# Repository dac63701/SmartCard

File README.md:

# Smart Card
A nRF54L15 based Bluetooth Tracker in a Credit Card sized package

The goal of this project was to create a small and slim Bluetooth tracker that would fit into a credit card enclosure. To do this, a 0.8mm thin 80mah battery was used along with a 0.8mm PCB. The device makes use of wireless charging with a BQ51013B so that it is easy to use and keep charged. There is also a custom battery charger and protection circuit. It uses a BQ298009 for protection and a BQ25100 for charging. Finally there is a TPS62840 for sourcing 1v8 from the battery and the antenna along with a matching network.

## Components
Check the [bom](https://github.com/dac63701/SmartCard/blob/main/production/bom.csv) for more details on the PCB components.
Standard PLA was used for the Prototype case.
The battery is a 084545 battery from [Alibaba](https://www.alibaba.com/product-detail/GEB-ultra-0-8mm-Thickness-084545_1601492203632.html?spm=a2756.trade-list-buyer.0.0.5fea76e93Ynkdn).

## Case Files
Check [OnShape](https://cad.onshape.com/documents/73dd8871ae024b497bb44b73/w/69cf76015be0ecbff129bf07/e/5547e5b9bb5f69b8ddd4b47d?renderMode=0&uiState=6a8e2710a56b25790309a2e5) for the files.

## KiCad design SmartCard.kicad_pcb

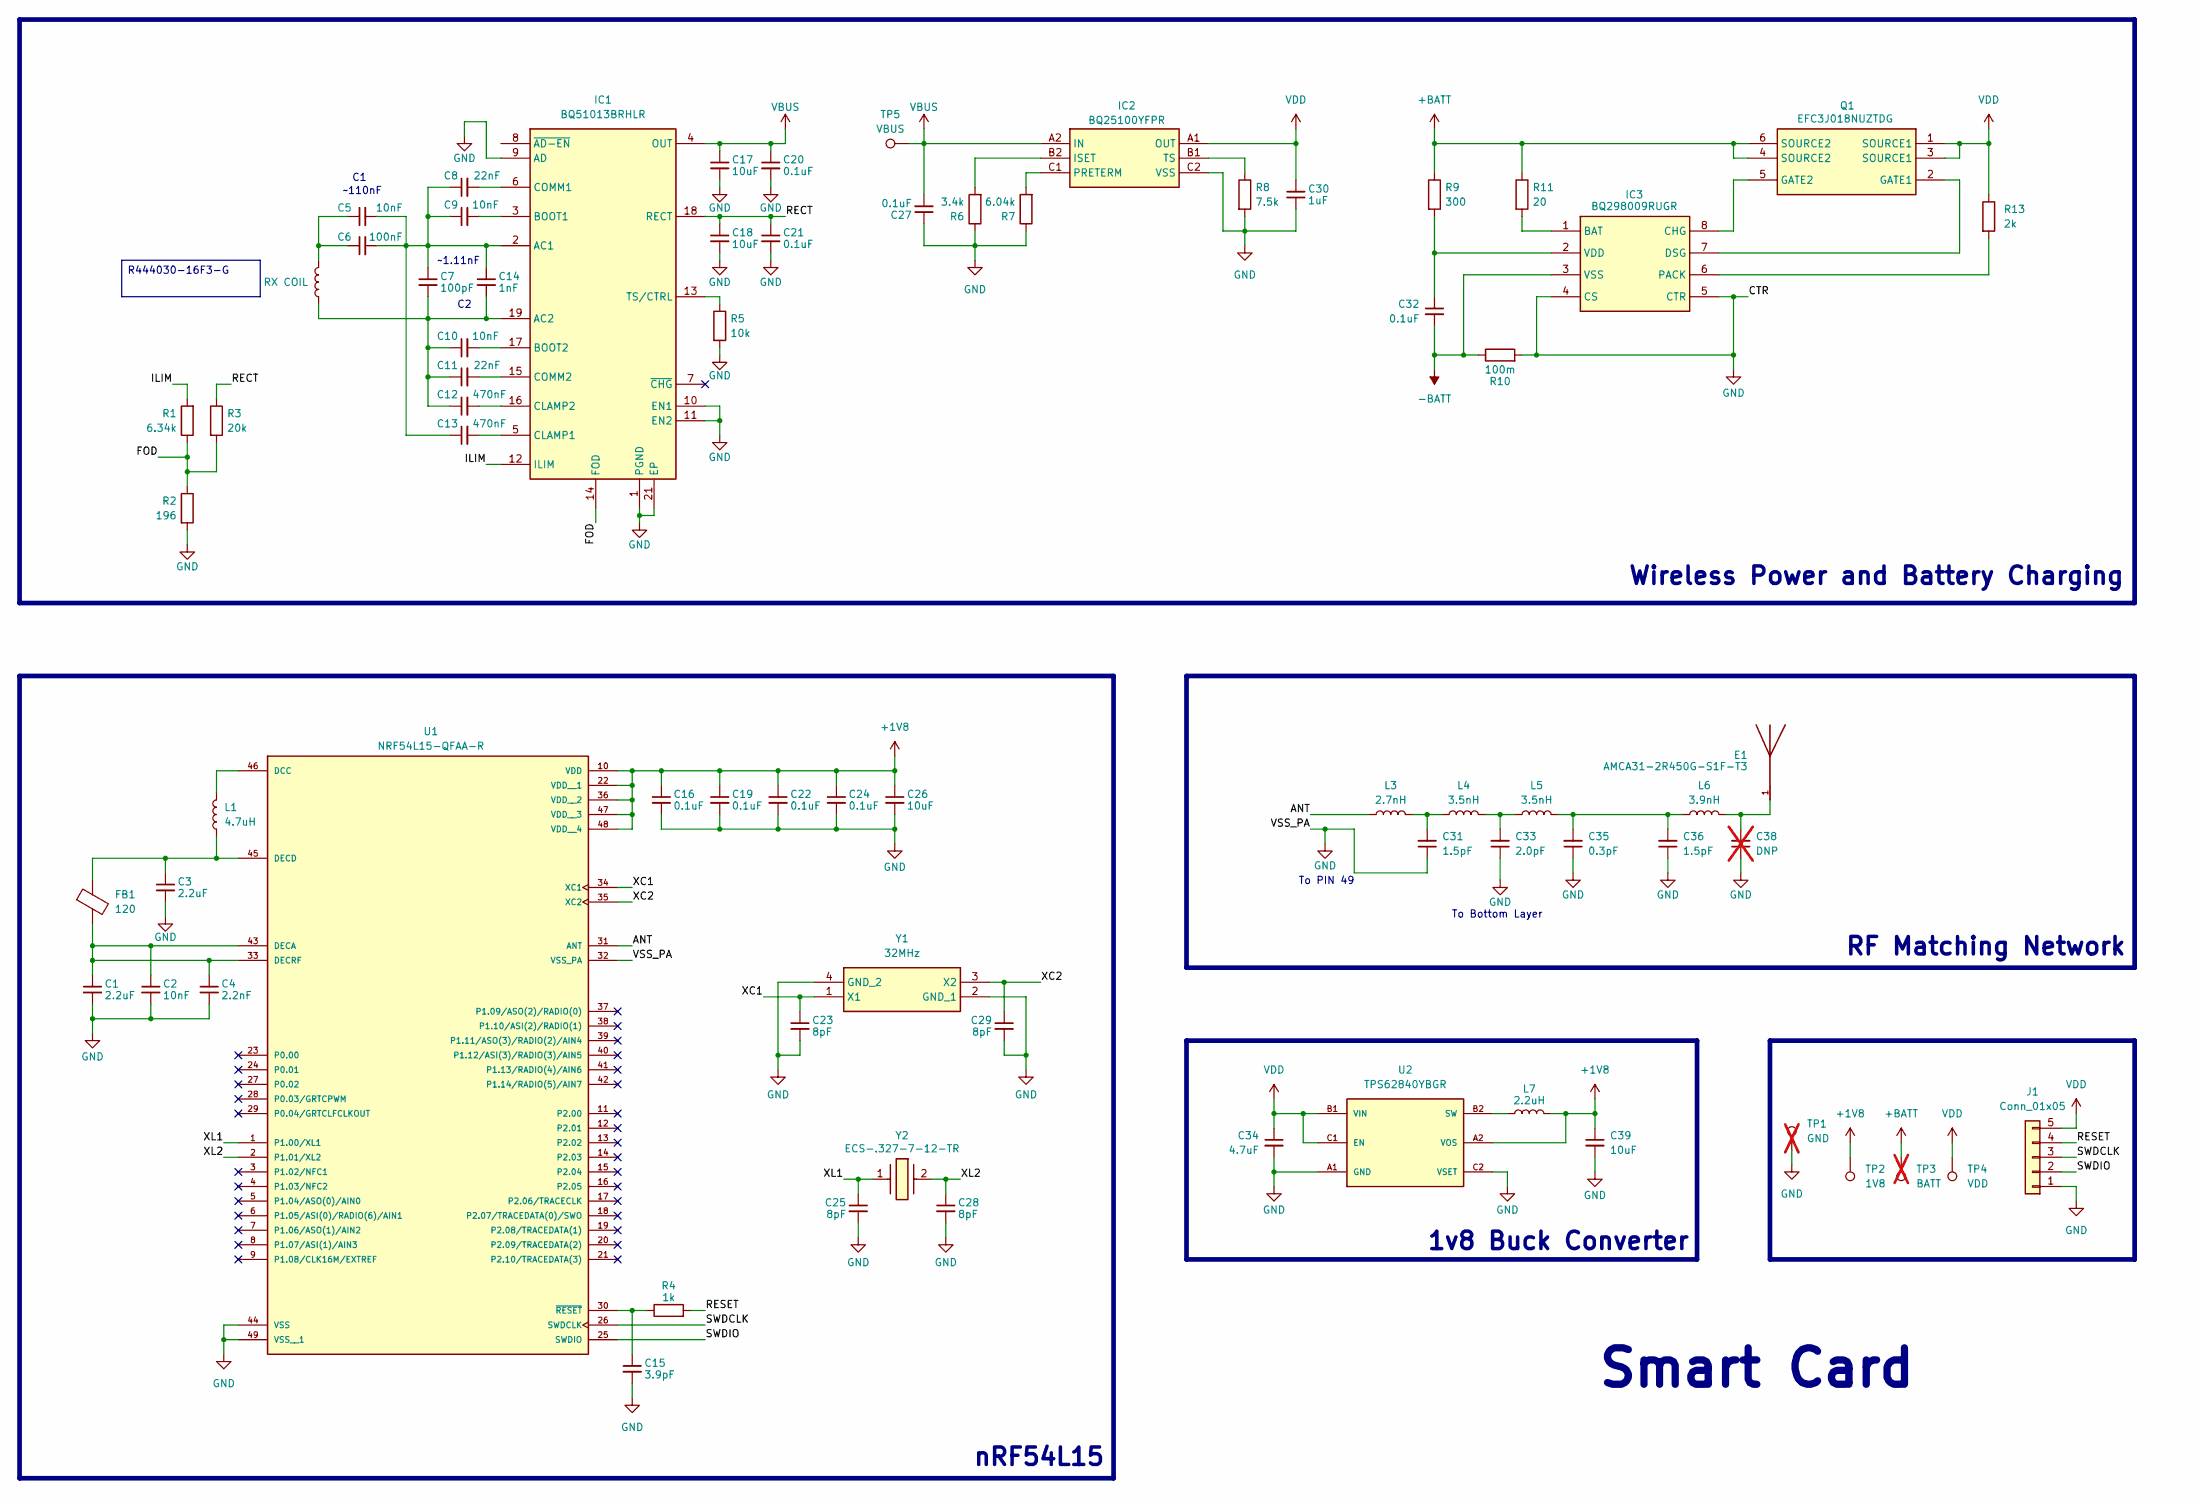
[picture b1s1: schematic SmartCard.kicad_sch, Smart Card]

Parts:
C1, C3: 2.2uF; C_0402_1005Metric; MPN GRM155D80J225ME95D
C2, C9, C10: 10nF; C_0402_1005Metric; MPN GRM155R71H103KA88D
C4: 2.2nF; C_0402_1005Metric; MPN GRM155R71C223KA01D
C5: 10nF; C_0603_1608Metric; MPN GRM155R71H103KA88D
C6: 100nF; C_0603_1608Metric; MPN GRM155R71H104KE14D
C7: 100pF; C_0603_1608Metric; MPN GRM155R71H331KA01D
C8, C11: 22nF; C_0402_1005Metric; MPN GRM155R71H223KA12D
C12, C13: 470nF; C_0402_1005Metric; MPN C1005X5R1E474K050BB
C14: 1nF; C_0603_1608Metric; MPN GRM155R71H102KA01D
C15: 3.9pF; C_0402_1005Metric; MPN GRM1555C1H3R9BA01D
C16, C19, C20, C21, C22, C24, C27, C32: 0.1uF; C_0402_1005Metric; MPN GRM155R71H104KE14D
C17, C18, C26, C39: 10uF; C_0603_1608Metric; MPN GRT188R61E106ME13D
C23, C25, C28, C29: 8pF; C_0402_1005Metric; MPN GJM1555C1H8R0BB01D
C30: 1uF; C_0603_1608Metric; MPN EMK105BJ105KV-F
C31, C36: 1.5pF; C_0201_0603Metric; MPN GJM0335C1E1R5WB01D
C33: 2.0pF; C_0201_0603Metric; MPN GRM0335C1H2R0WA01D
C34: 4.7uF; C_0603_1608Metric; MPN GMC10X5R475K10NT
C35: 0.3pF; C_0201_0603Metric; MPN GRM0335C1ER30WA01D
C38: DNP; C_0201_0603Metric; MPN DNP; not fitted
E1: AMCA31-2R450G-S1F-T3; XDCR_AMCA31-2R450G-S1F-T3; PARTREV 03-21-19
FB1: 120; L_0402_1005Metric; MPN 2504021217Y0
IC1: BQ51013BRHLR; Texas_VQFN-RHL-20; Mouser Part Number 595-BQ51013BRHLR
IC2: BQ25100YFPR; BGA6C40P2X3_88X158X50; Mouser Part Number 595-BQ25100YFPR
IC3: BQ298009RUGR; Mouser Part Number 595-BQ298009RUGR
J1: Conn_01x05; PinHeader_1x05_P2.54mm_Vertical
L1: 4.7uH; L_0603_1608Metric; MPN MLZ1608CWC4R7MTD25
L2: RX COIL; L_1812_4532Metric_Pad1.30x3.40mm_HandSolder; MPN WR444030-16F3-G
L3: 2.7nH; L_0201_0603Metric; MPN LQP03HQ2N7B02D
L4, L5: 3.5nH; L_0201_0603Metric; MPN LQP03HQ3N5B02D
L6: 3.9nH; L_0201_0603Metric; MPN LQP03TQ3N9B02D
L7: 2.2uH; L_0603_1608Metric; MPN LQM18PN2R2MGHD
Q1: EFC3J018NUZTDG; Mouser Part Number 863-EFC3J018NUZTDG
R1: 6.34k; R_0402_1005Metric; MPN RC0402FR-076K34L
R2: 196; R_0402_1005Metric; MPN CRCW0402196RFKED
R3: 20k; R_0402_1005Metric; MPN RC0402FR-0720KL
R4: 1k; R_0402_1005Metric; MPN RC0402FR-071KL
R5: 10k; R_0402_1005Metric; MPN RC0402FR-0710KL
R6: 3.4k; R_0402_1005Metric; MPN RC0402FR-073K4L
R7: 6.04k; R_0402_1005Metric; MPN RC0402FR-076K04L
R8: 7.5k; R_0402_1005Metric; MPN RC0402FR-077K5L
R9: 300; R_0402_1005Metric; MPN RC0402FR-07300RL
R10: 100m; R_0805_2012Metric; MPN RL1220S-R10-F
R11: 20; R_0402_1005Metric; MPN RC0402FR-0720RL
R13: 2k; R_0402_1005Metric; MPN RC0402FR-0720KL
TP1: GND; TestPoint_Pad_2.0x2.0mm; not fitted
TP2: 1V8; TestPoint_Pad_2.0x2.0mm
TP3: BATT; TestPoint_Pad_2.0x2.0mm; not fitted
TP4: VDD; TestPoint_Pad_2.0x2.0mm
TP5: VBUS; TestPoint_Pad_2.0x2.0mm
U1: NRF54L15-QFAA-R; QFN40P600X600X90-49N; PARTREV 0.8
U2: TPS62840YBGR; PARTREV D
Y1: 32MHz; ABM11W300000MHZ4B1UT3; Manufacturer_Part_Number ABM11W-25.0000MHZ-7-D1X-T3
Y2: ECS-.327-7-12-TR; ECS327712TR; Mouser Part Number 520-ECS-.327-7-12-TR

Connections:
+1V8: C16.1, C19.1, C22.1, C24.1, C26.1, C39.1, L7.2, TP2.1 (1_1), U1.10 (VDD), U1.22 (VDD__1), U1.36 (VDD__2), U1.47 (VDD__3), U1.48 (VDD__4), U2.A2 (VOS)
+BATT: Q1.4 (SOURCE2), Q1.6 (SOURCE2), R9.1, R11.1, TP3.1
-BATT: C32.2, IC3.3 (VSS), R10.1
/ANT: L3.1, U1.31 (ANT)
/FOD: IC1.14 (FOD), R1.1, R2.1, R3.2
/ILIM: IC1.12 (ILIM), R1.2
/RECT: C18.1, C21.1, IC1.18 (RECT), R3.1
/RESET: J1.4, R4.2
/SWDCLK: J1.3, U1.26 (SWDCLK)
/SWDIO: J1.2, U1.25 (SWDIO)
/XC1: C23.1, U1.34 (XC1), Y1.1 (X1)
/XC2: C29.1, U1.35 (XC2), Y1.3 (X2)
/XL1: C25.1, U1.1 (P1.00/XL1), Y2.1
/XL2: C28.1, U1.2 (P1.01/XL2), Y2.2 (OUT/IN_2)
GND: C1.2, C2.2, C3.2, C4.2, C15.2, C16.2, C17.2, C18.2, C19.2, C20.2, C21.2, C22.2, C23.2, C24.2, C25.2, C26.2, C27.1, C28.2, C29.2, C30.2, C31.1, C33.1, C34.2, C35.1, C36.1, C38.1, C39.2, IC1.1 (PGND), IC1.9 (AD), IC1.10 (EN1), IC1.11 (EN2), IC1.20 (PGND), IC1.21 (EP), IC2.C2 (VSS), IC3.4 (CS), IC3.5 (CTR), J1.1, R2.2, R5.2, R6.1, R7.1, R8.2, R10.2, TP1.1, U1.32 (VSS_PA), U1.44 (VSS), U1.49 (VSS__1), U2.A1 (GND), U2.C2 (VSET), Y1.2 (GND_1), Y1.4 (GND_2)
unnamed: C5.1, C6.1, L2.2
unnamed: C31.2, L3.2, L4.1
unnamed: C33.2, L4.2, L5.1
unnamed: C35.2, C36.2, L5.2, L6.1
unnamed: C38.2, E1.1, L6.2
unnamed: C5.2, C6.2, C7.1, C8.1, C9.1, C13.1, C14.1, IC1.2 (AC1)
unnamed: C7.2, C10.1, C11.1, C12.1, C14.2, IC1.19 (AC2), L2.1
unnamed: C9.2, IC1.3 (BOOT1)
unnamed: C10.2, IC1.17 (BOOT2)
unnamed: C13.2, IC1.5 (CLAMP1)
unnamed: C12.2, IC1.16 (CLAMP2)
unnamed: C8.2, IC1.6 (COMM1)
unnamed: C11.2, IC1.15 (COMM2)
unnamed: IC1.13 (TS/CTRL), R5.1
unnamed: IC2.B2 (ISET), R6.2
unnamed: IC2.C1 (PRETERM), R7.2
unnamed: IC2.B1 (TS), R8.1
unnamed: IC3.1 (BAT), R11.2
unnamed: IC3.8 (CHG), Q1.5 (GATE2)
unnamed: IC3.7 (DSG), Q1.2 (GATE1)
unnamed: IC3.6 (PACK), R13.2
unnamed: C32.1, IC3.2 (VDD), R9.2
unnamed: L1.2, U1.46 (DCC)
unnamed: C1.1, C2.1, C4.1, FB1.2, U1.33 (DECRF), U1.43 (DECA)
unnamed: C3.1, FB1.1, L1.1, U1.45 (DECD)
unnamed: C15.1, R4.1, U1.30 (~RESET)
unnamed: L7.1, U2.B2 (SW)
VBUS: C17.1, C20.1, C27.2, IC1.4 (OUT), IC2.A2 (IN), TP5.1 (1_1)
VDD: C30.1, C34.1, IC2.A1 (OUT), J1.5, Q1.1 (SOURCE1), Q1.3 (SOURCE1), R13.1, TP4.1 (1_1), U2.B1 (VIN), U2.C1 (EN)

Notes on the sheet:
~1.11nF
nRF54L15
1v8 Buck Converter
~110nF
Wireless Power and Battery Charging
RF Matching Network
To PIN 49
To Bottom Layer
Smart Card
R444030-16F3-G

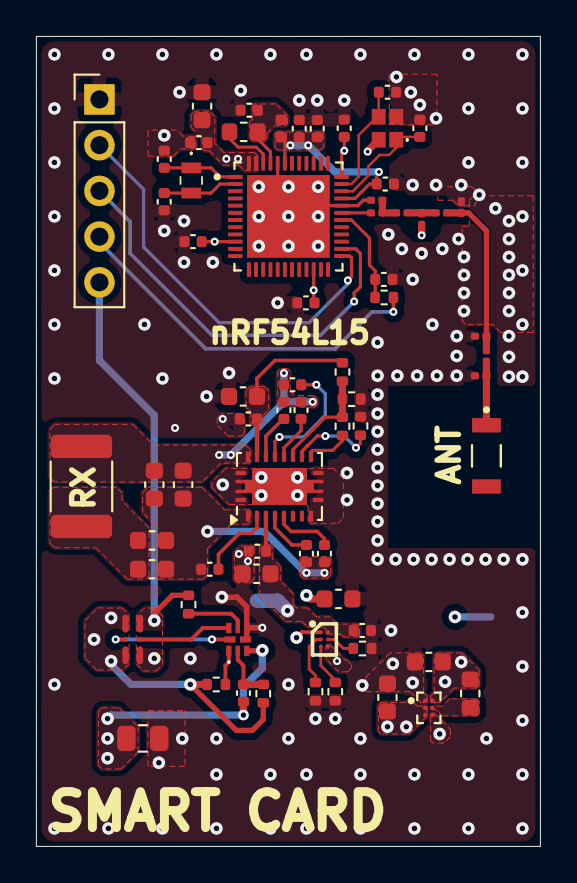
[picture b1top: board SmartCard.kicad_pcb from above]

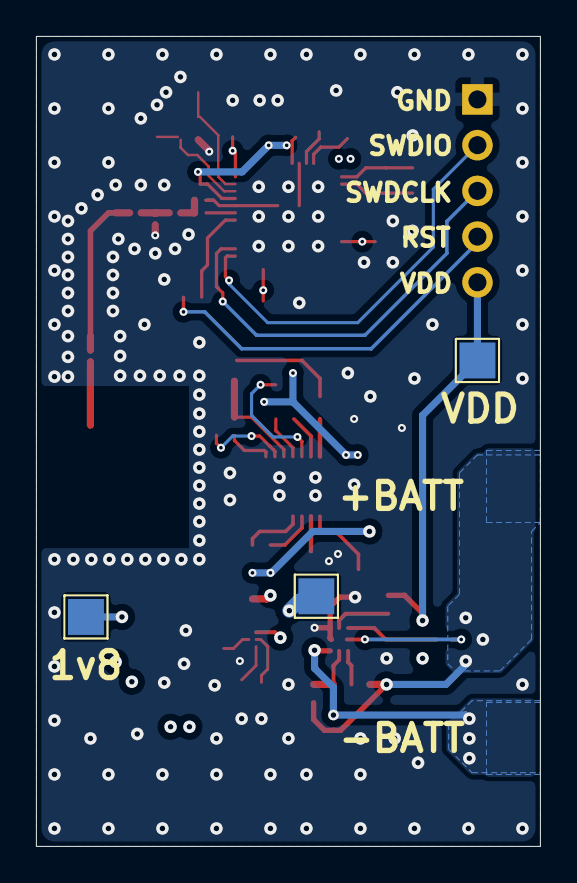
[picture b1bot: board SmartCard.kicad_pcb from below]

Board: 4 copper layers, 28.0 x 45.0 mm, 71 parts (3 on the bottom side), 44 nets.

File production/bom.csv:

Designator,Footprint,Quantity,Value,LCSC Part #
"C1, C3",0402,2,2.2uF,GRM155D80J225ME95D
"C10, C2, C9",0402,3,10nF,GRM155R71H103KA88D
"C11, C8",0402,2,22nF,GRM155R71H223KA12D
"C12, C13",0402,2,470nF,C1005X5R1E474K050BB
C14,0603,1,1nF,GRM155R71H102KA01D
C15,0402,1,3.9pF,GRM1555C1H3R9BA01D
"C16, C19, C20, C21, C22, C24, C27, C32",0402,8,0.1uF,GRM155R71H104KE14D
"C17, C18, C26, C39",0603,4,10uF,GRT188R61E106ME13D
"C23, C25, C28, C29",0402,4,8pF,GJM1555C1H8R0BB01D
C30,0603,1,1uF,EMK105BJ105KV-F
"C31, C36",0201,2,1.5pF,GJM0335C1E1R5WB01D
C33,0201,1,2.0pF,GRM0335C1H2R0WA01D
C34,0603,1,4.7uF,GMC10X5R475K10NT
C35,0201,1,0.3pF,GRM0335C1ER30WA01D
C4,0402,1,2.2nF,GRM155R71C223KA01D
C5,0603,1,10nF,GRM155R71H103KA88D
C6,0603,1,100nF,GRM155R71H104KE14D
C7,0603,1,100pF,GRM155R71H331KA01D
E1,XDCR_AMCA31-2R450G-S1F-T3,1,AMCA31-2R450G-S1F-T3,AMCA31-2R450G-S1F-T3
FB1,0402,1,120,2504021217Y0
IC1,Texas_VQFN-RHL-20,1,BQ51013BRHLR,BQ51013BRHLR
IC2,BGA6C40P2X3_88X158X50,1,BQ25100YFPR,BQ25100YFPR
IC3,BQ298009RUGR,1,BQ298009RUGR,BQ298009RUGR
L1,0603,1,4.7uH,MLZ1608CWC4R7MTD25
L2,1812,1,RX COIL,WR444030-16F3-G
L3,0201,1,2.7nH,LQP03HQ2N7B02D
"L4, L5",0201,2,3.5nH,LQP03HQ3N5B02D
L6,0201,1,3.9nH,LQP03TQ3N9B02D
L7,0603,1,2.2uH,LQM18PN2R2MGHD
Q1,EFC3J018NUZTDG,1,EFC3J018NUZTDG,EFC3J018NUZTDG
R1,0402,1,6.34k,RC0402FR-076K34L
R10,0805,1,100m,RL1220S-R10-F
R11,0402,1,20,RC0402FR-0720RL
R13,0402,1,2k,RC0402FR-0720KL
R2,0402,1,196,CRCW0402196RFKED
R3,0402,1,20k,RC0402FR-0720KL
R4,0402,1,1k,RC0402FR-071KL
R5,0402,1,10k,RC0402FR-0710KL
R6,0402,1,3.4k,RC0402FR-073K4L
R7,0402,1,6.04k,RC0402FR-076K04L
R8,0402,1,7.5k,RC0402FR-077K5L
R9,0402,1,300,RC0402FR-07300RL
U1,QFN40P600X600X90-49N,1,NRF54L15-QFAA-R,NRF54L15-QFAA-R
U2,TPS62840YBGR,1,TPS62840YBGR,TPS62840YBGR
Y1,ABM11W300000MHZ4B1UT3,1,32MHz,ABM11W-32.0000MHZ-7-D1X-T3
Y2,ECS327712TR,1,ECS-.327-7-12-TR,ECS-.327-7-12-TR

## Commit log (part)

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2026-05-07 Refactor KiCad schematic symbols & positions
    Adjust schematic symbols and component placements in SmartCard.kicad_sch and update project metadata in SmartCard.kicad_pro. Changes include repositioning pins and boxes for multiple components (e.g.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
2026-05-11 Update KiCad schematic symbols & add backups
    Add three SmartCard backup zip files and update the KiCad project files. SmartCard.kicad_sch: introduce new/updated library symbols (Abracon AMCA31 transducer, ABM11W oscillator replacing a prior par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
2026-06-05 Update KiCad prefs, board rules, schematic
    Add backup zips and update KiCad project files: expand net inspector column settings in SmartCard.kicad_prl; add comprehensive design_settings (DRC/rules, teardrops, track/tuning defaults, via/zones)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
